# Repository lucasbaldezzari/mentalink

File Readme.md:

# Repositorio Mentalink para competencia BCI

El siguiente repositorio será utilizado para almacenar bibliografía, set de datos, firmware, hardware, imágenes, entre otras cosas, las cuales utilizarán para dictar diferentes talleres y ayduar a los equipos a adquirir y procesar señales de EEG para detectar SSVEPs

## Talleres

- [x] Taller 1: Introducción a las Interfaces Cerebro Computadora
- [x] Taller 2: Introducción a la adquisición y procesamiento de SSVEP
- [x] Taller 3: Introducción a Arduino y Robótica
- [x] Taller 4: Aplicando una CNN para clasificar datos
- [x] Taller 5: Comunicación entre PC y Arduino mediante Python para sincronizar estímulos y recepción/envío de información.  Comunicación entre Python y sitio en HTML para sincronizar estímulos. Protocolo de adquisición de señales de EEG para entrenar clasificadores que serán utilizados en la BCI de manera online. Manejo de versiones en archivos de firmware y hardware.
- [x] Taller 6: Adquisición, procesamiento y almacenamiento de señales de EEG provenientes de la placa Cyton Board de OpenBCI usando Python. Análisis de datos obtenidos luego de la sesión de entrenamiento.

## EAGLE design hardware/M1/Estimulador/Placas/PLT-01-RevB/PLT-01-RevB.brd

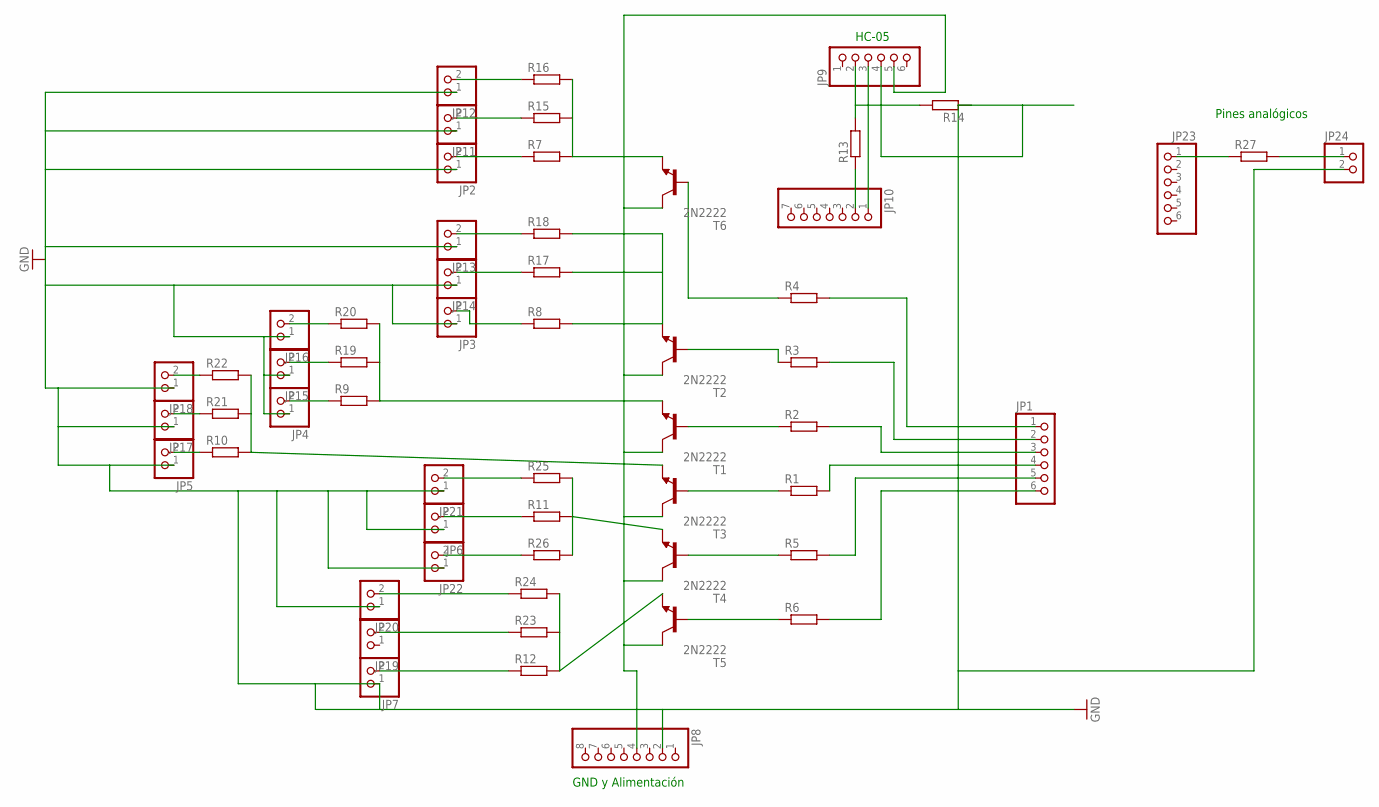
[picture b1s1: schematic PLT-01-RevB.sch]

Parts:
JP1, JP9, JP23: PINHD-1X6; 1X06
JP2, JP3, JP4, JP5, JP6, JP7, JP11, JP12, JP13, JP14, JP15, JP16, JP17, JP18, JP19, JP20, JP21, JP22, JP24: PINHD-1X2; 1X02
JP8: PINHD-1X8; 1X08
JP10: PINHD-1X7; 1X07
R1, R2, R3, R4, R5, R6, R7, R8, R9, R10, R11, R12, R13, R14, R15, R16, R17, R18, R19, R20, R21, R22, R23, R24, R25, R26, R27: R-EU_0207/10; 0207/10
T1, T2, T3, T4, T5, T6: 2N2222; TO92-EBC-OVAL

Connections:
5V: JP8.4, JP9.5, T1.C, T2.C, T3.C, T4.C, T5.C, T6.C
GND: JP2.1, JP3.1, JP4.1, JP5.1, JP6.1, JP7.1, JP8.2, JP9.4, JP11.1, JP12.1, JP13.1, JP14.1, JP15.1, JP16.1, JP17.1, JP18.1, JP20.1, JP21.1, JP22.1, JP24.2, R14.1
unnamed: JP1.1, R4.2
unnamed: JP1.2, R3.2
unnamed: JP1.3, R2.2
unnamed: JP1.4, R1.2
unnamed: JP1.5, R5.2
unnamed: JP1.6, R6.2
unnamed: R6.1, T5.B
unnamed: R5.1, T4.B
unnamed: R1.1, T3.B
unnamed: R2.1, T1.B
unnamed: R3.1, T2.B
unnamed: R4.1, T6.B
unnamed: R7.2, R15.2, R16.2, T6.E
unnamed: JP2.2, R7.1
unnamed: R8.2, R17.2, R18.2, T2.E
unnamed: JP3.2, R8.1
unnamed: R9.2, R19.2, R20.2, T1.E
unnamed: JP4.2, R9.1
unnamed: R10.2, R21.2, R22.2, T3.E
unnamed: JP5.2, R10.1
unnamed: R11.2, R25.2, R26.2, T4.E
unnamed: JP6.2, R11.1
unnamed: R12.2, R23.2, R24.2, T5.E
unnamed: JP7.2, R12.1
unnamed: JP10.2, R13.1
unnamed: JP9.2, R13.2, R14.2
unnamed: JP9.3, JP10.1
unnamed: JP13.2, R18.1
unnamed: JP14.2, R17.1
unnamed: JP17.2, R21.1
unnamed: JP18.2, R22.1
unnamed: JP19.2, R23.1
unnamed: JP20.2, R24.1
unnamed: JP21.2, R25.1
unnamed: JP22.2, R26.1
unnamed: JP12.2, R16.1
unnamed: JP11.2, R15.1
unnamed: JP16.2, R20.1
unnamed: JP15.2, R19.1
unnamed: JP23.1, R27.1
unnamed: JP24.1, R27.2

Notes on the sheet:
Pines analógicos
HC-05
GND y Alimentación

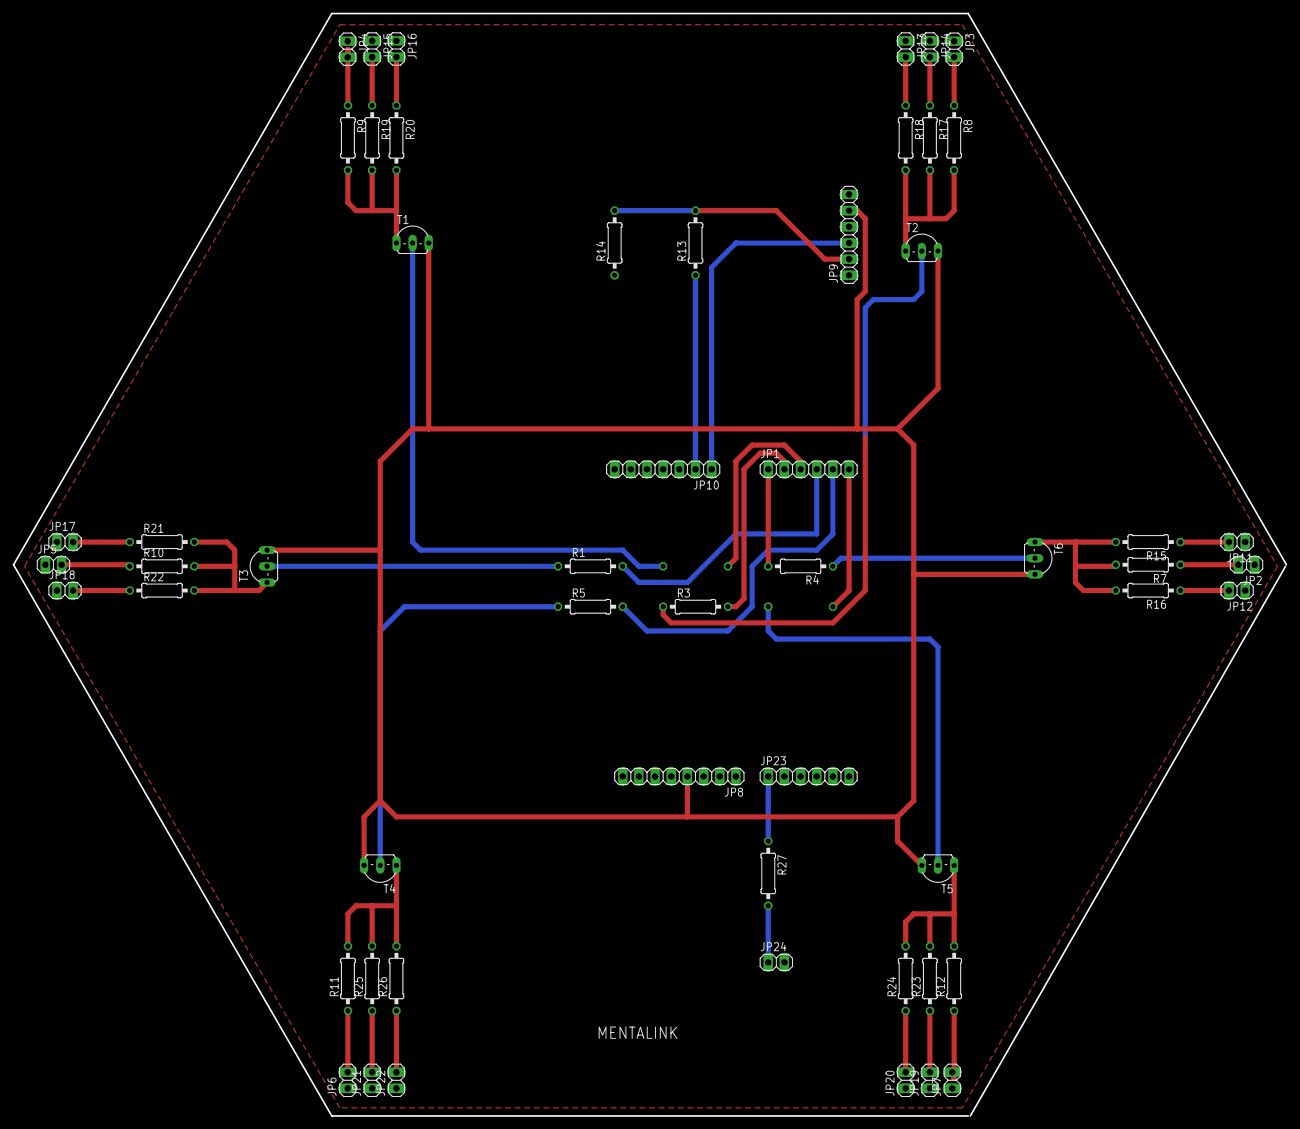
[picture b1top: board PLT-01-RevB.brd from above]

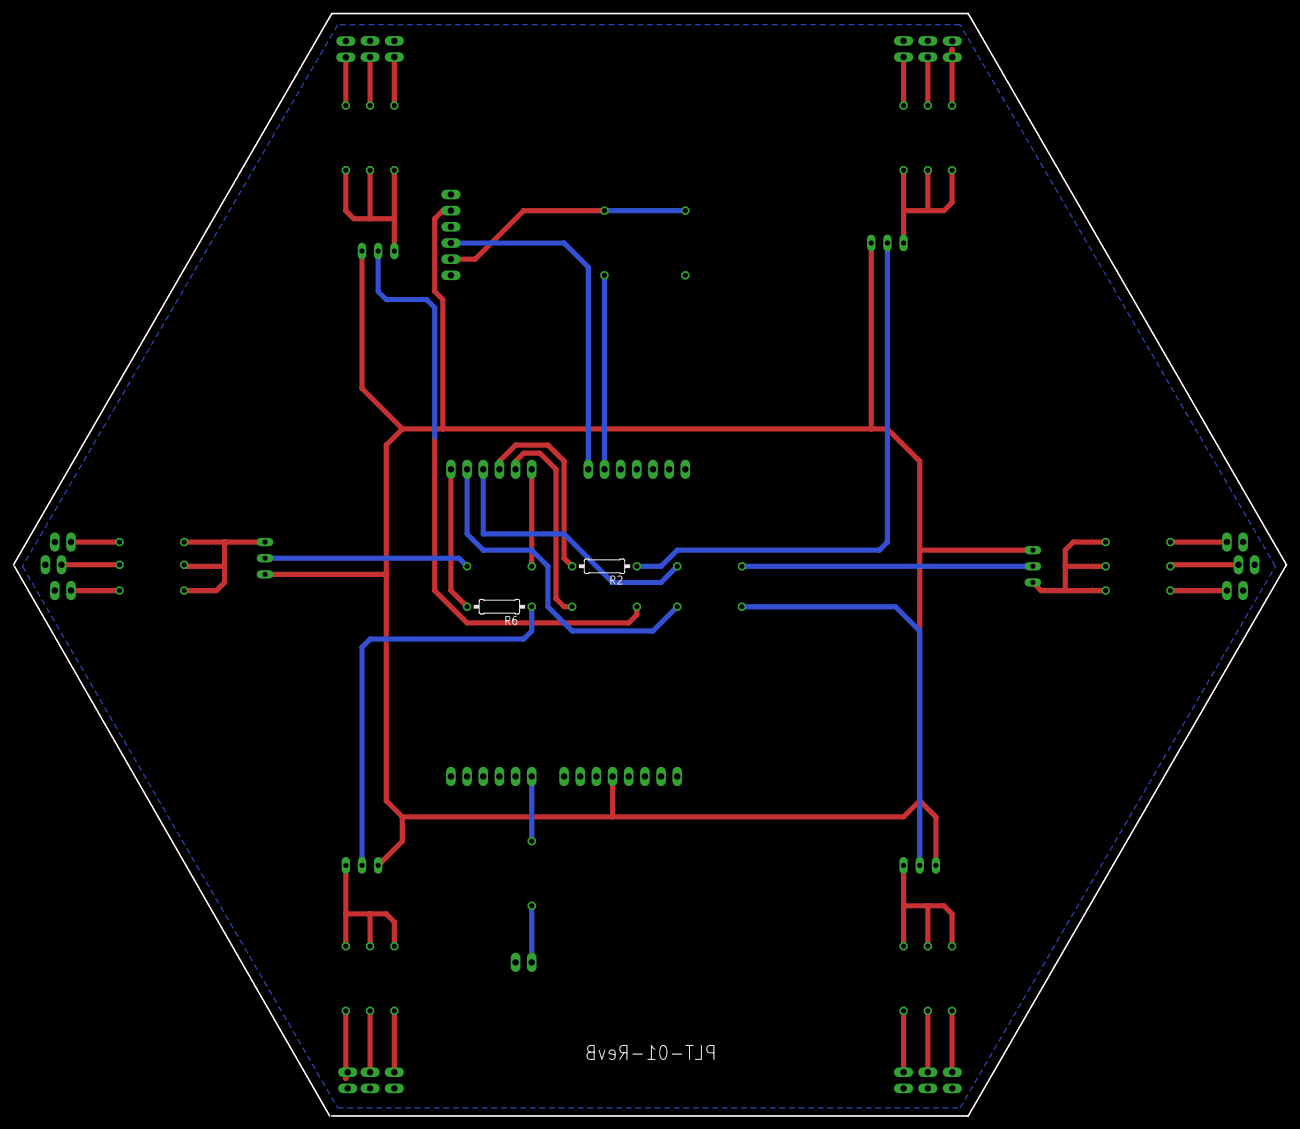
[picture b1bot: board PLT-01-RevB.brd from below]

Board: 2 copper layers, 200.0 x 173.2 mm, 57 parts (2 on the bottom side), 43 nets.

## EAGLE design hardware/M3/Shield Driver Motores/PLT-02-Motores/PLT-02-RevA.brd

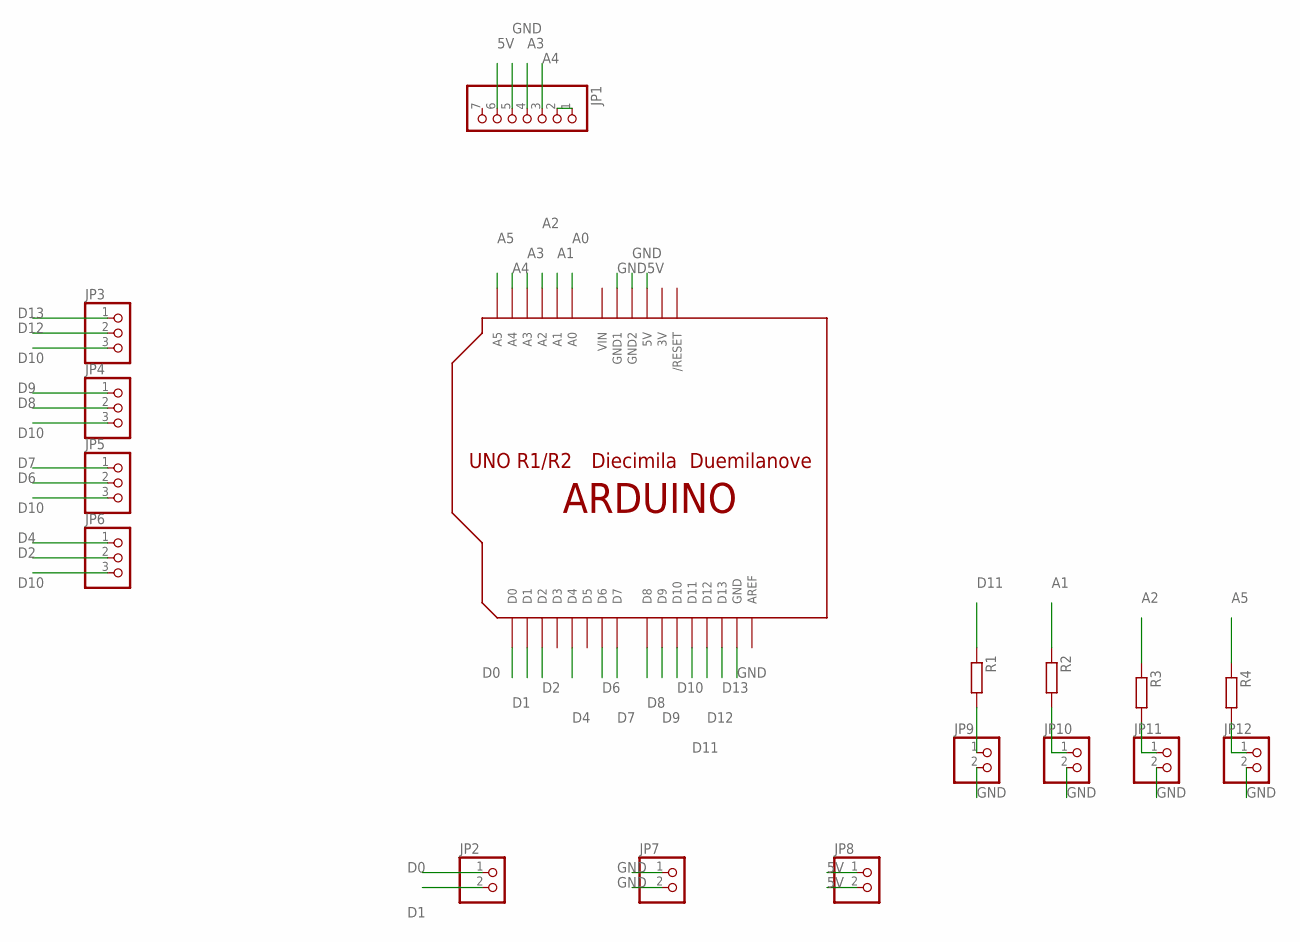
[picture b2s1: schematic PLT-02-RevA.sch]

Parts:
JP1: PINHD-1X7; 1X07
JP2, JP7, JP8, JP9, JP10, JP11, JP12: PINHD-1X2; 1X02
JP3, JP4, JP5, JP6: PINHD-1X3; 1X03
R1, R2, R3, R4: R-EU_0207/10; 0207/10
U$1: ARDUINOUNO; ARDUINO

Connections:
3V: U$1.3V
5V: JP1.6, JP8.1, JP8.2, U$1.5V
A0: U$1.A0
A1: R2.1, U$1.A1
A2: R3.1, U$1.A2
A3: JP1.4, U$1.A3
A4: JP1.3, U$1.A4
A5: R4.1, U$1.A5
D0: JP2.1, U$1.D0
D1: JP2.2, U$1.D1
D2: JP6.2, U$1.D2
D4: JP6.1, U$1.D4
D6: JP5.2, U$1.D6
D7: JP5.1, U$1.D7
D8: JP4.2, U$1.D8
D9: JP4.1, U$1.D9
D10: JP3.3, JP4.3, JP5.3, JP6.3, U$1.D10
D11: R1.1, U$1.D11
D12: JP3.2, U$1.D12
D13: JP3.1, U$1.D13
GND: JP1.5, JP7.1, JP7.2, JP9.2, JP10.2, JP11.2, JP12.2, U$1.GND, U$1.GND1, U$1.GND2
unnamed: JP12.1, R4.2
unnamed: JP10.1, R2.2
unnamed: JP11.1, R3.2
unnamed: JP1.1, JP1.2
unnamed: JP9.1, R1.2
VIN: U$1.VIN

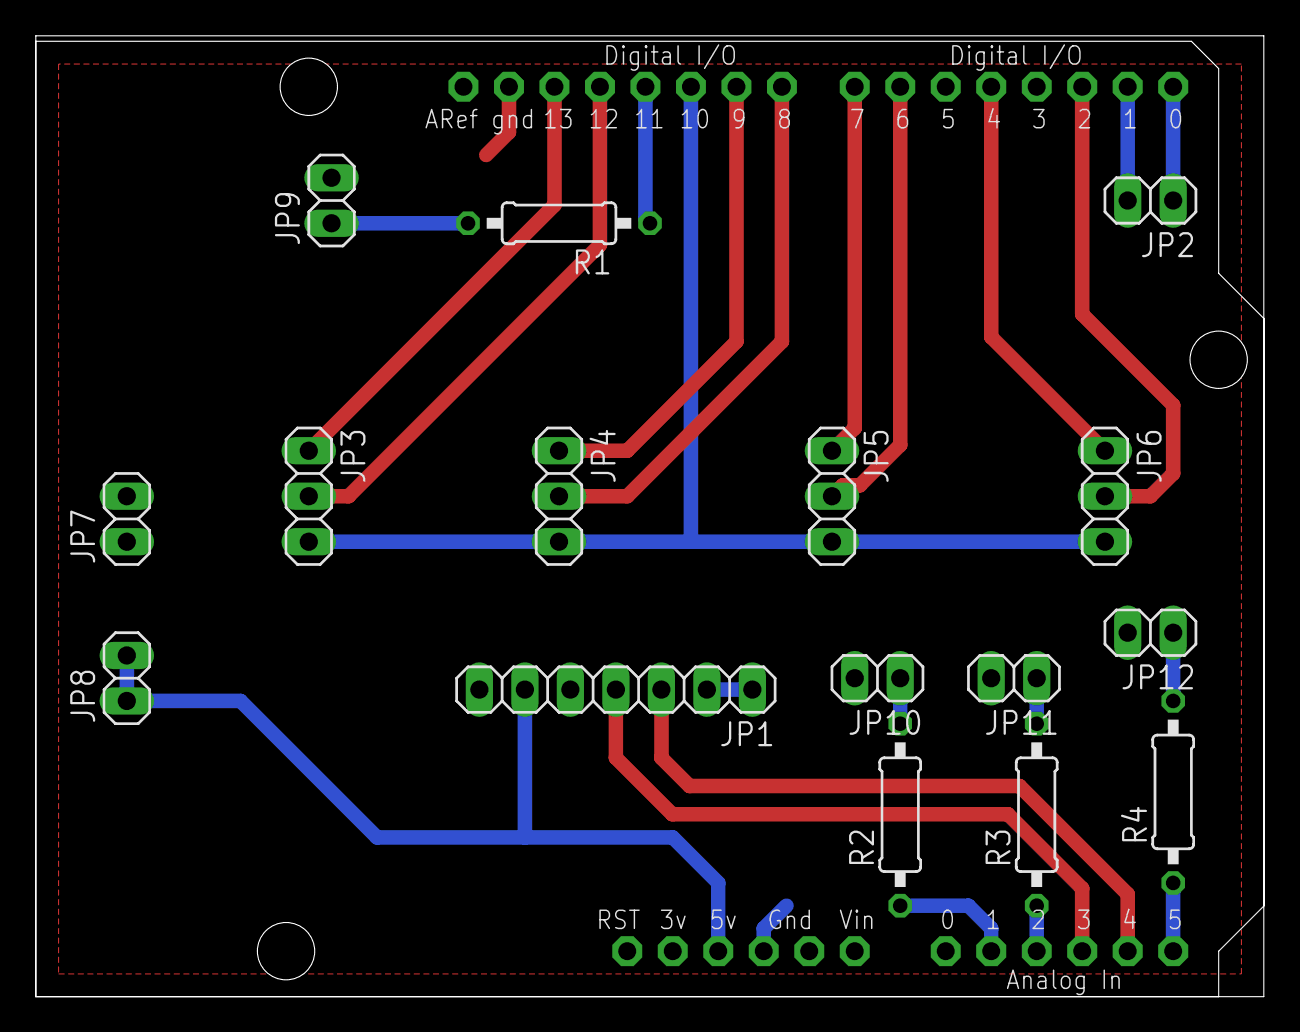
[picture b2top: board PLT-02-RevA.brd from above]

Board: 2 copper layers, 68.6 x 53.6 mm, 17 parts (0 on the bottom side), 24 nets.

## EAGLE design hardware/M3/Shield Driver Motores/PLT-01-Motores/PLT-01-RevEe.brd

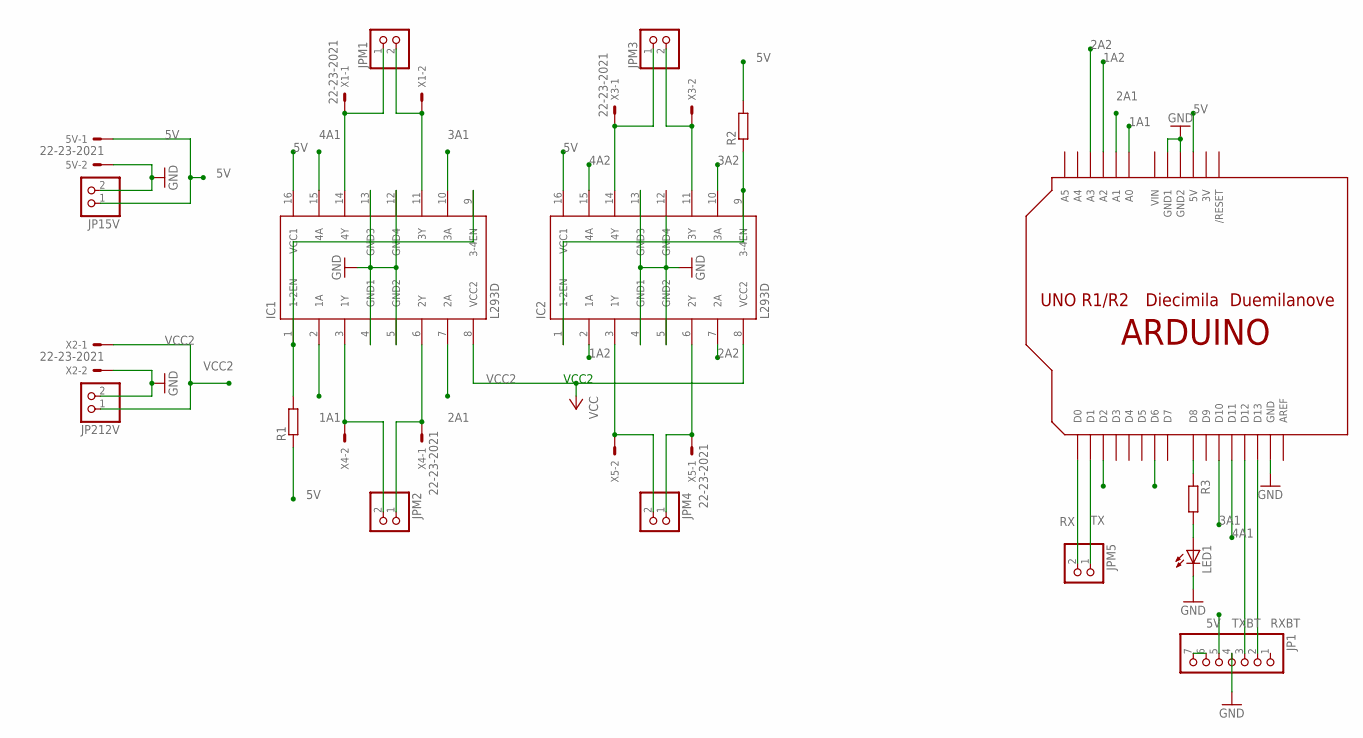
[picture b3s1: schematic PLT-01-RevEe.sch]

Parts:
5V: 22-23-2021
IC1, IC2: L293D; DIL16
JP1: PINHD-1X7; 1X07
JP15V, JP212V: PINHD-1X2; 1X02
JPM1, JPM2, JPM3, JPM4, JPM5: PINHD-1X2; 1X02
LED1: LED5MM
R1, R2, R3: R-EU_0207/10; 0207/10
U$1: ARDUINOUNO; ARDUINO
X1, X2, X3, X4, X5: 22-23-2021

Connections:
1A1: IC1.2 (1A), U$1.A0
1A2: IC2.2 (1A), U$1.A2
2A1: IC1.7 (2A), U$1.A1
2A2: IC2.7 (2A), U$1.A3
3A1: IC1.10 (3A), U$1.D10
3A2: IC2.10 (3A), U$1.D2
3V: U$1.3V
4A1: IC1.15 (4A), U$1.D11
4A2: IC2.15 (4A), U$1.D6
5V: 5V.1, IC1.16 (VCC1), IC2.16 (VCC1), JP1.5, JP15V.1, R1.1, R2.2, U$1.5V
GND: 5V.2, IC1.4 (GND1), IC1.5 (GND2), IC1.12 (GND4), IC1.13 (GND3), IC2.4 (GND1), IC2.5 (GND2), IC2.13 (GND3), JP1.4, JP15V.2, JP212V.2, LED1.K (C), U$1.GND, U$1.GND1, U$1.GND2, X2.2
GND4: IC2.12 (GND4)
unnamed: IC1.3 (1Y), JPM2.2, X4.2
unnamed: IC1.6 (2Y), JPM2.1, X4.1
unnamed: IC2.3 (1Y), JPM4.2, X5.2
unnamed: IC2.6 (2Y), JPM4.1, X5.1
unnamed: IC2.14 (4Y), JPM3.1, X3.1
unnamed: IC2.11 (3Y), JPM3.2, X3.2
unnamed: IC1.14 (4Y), JPM1.1, X1.1
unnamed: IC1.11 (3Y), JPM1.2, X1.2
unnamed: IC2.1 (1-2EN), IC2.9 (3-4EN), R2.1
unnamed: R3.1, U$1.D8
unnamed: IC1.1 (1-2EN), IC1.9 (3-4EN), R1.2
unnamed: LED1.A, R3.2
unnamed: JP1.6, JP1.7
RX: JPM5.2, U$1.D0
RXBT: JP1.2, U$1.D13
TX: JPM5.1, U$1.D1
TXBT: JP1.3, U$1.D12
VCC2: IC1.8 (VCC2), IC2.8 (VCC2), JP212V.1, X2.1
VIN: U$1.VIN

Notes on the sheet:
VCC2

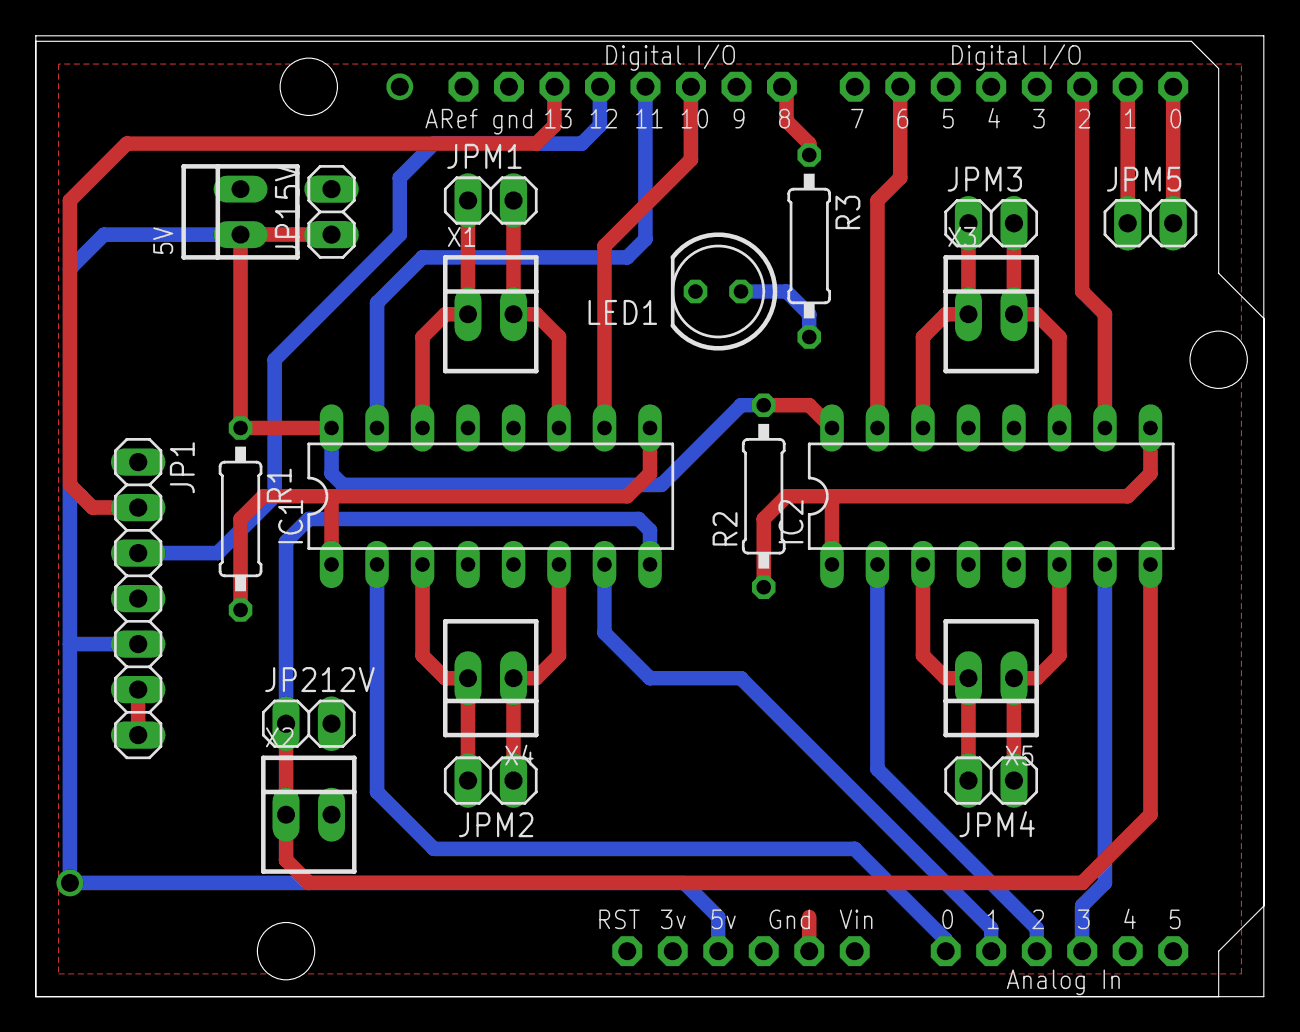
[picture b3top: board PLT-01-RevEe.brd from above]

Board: 2 copper layers, 68.6 x 53.6 mm, 21 parts (0 on the bottom side), 28 nets.

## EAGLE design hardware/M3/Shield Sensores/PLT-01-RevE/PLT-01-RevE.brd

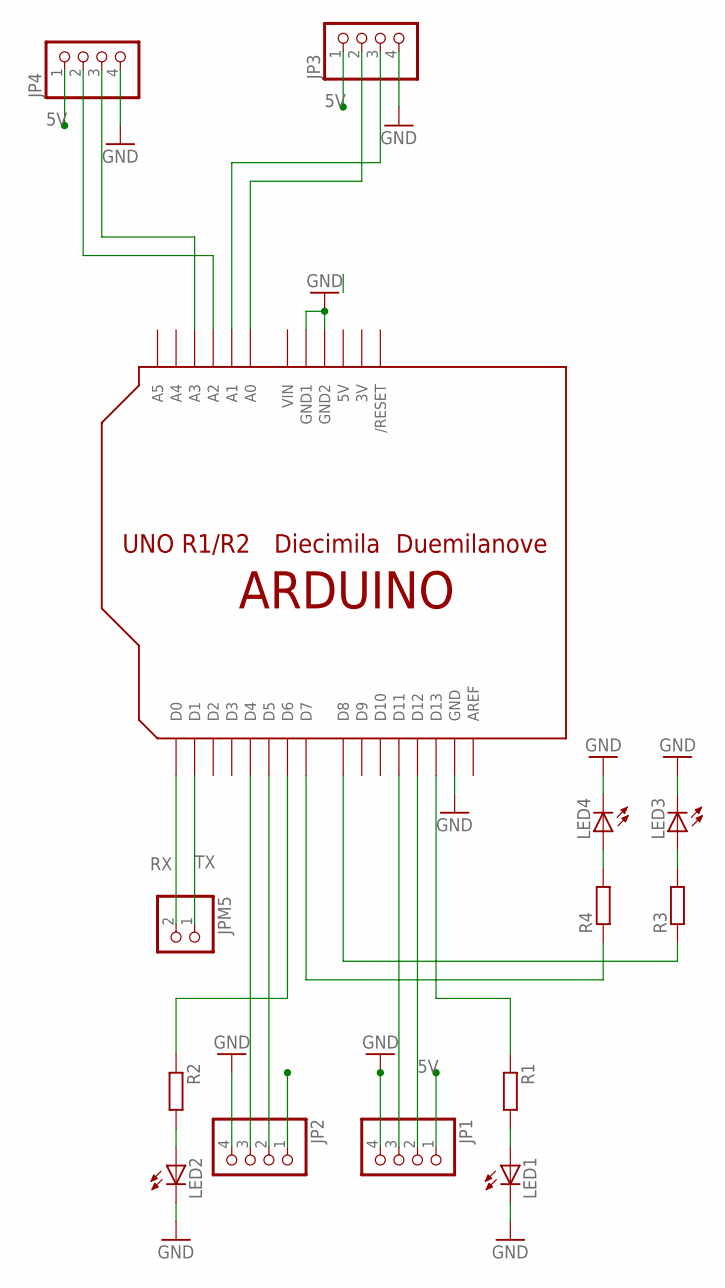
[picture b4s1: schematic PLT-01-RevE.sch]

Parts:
JP1, JP2, JP3, JP4: PINHD-1X4; 1X04
JPM5: PINHD-1X2; 1X02
LED1, LED2, LED3, LED4: LED5MM
R1, R2, R3, R4: R-EU_0207/10; 0207/10
U$1: ARDUINOUNO; ARDUINO

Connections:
3V: U$1.3V
5V: JP1.1, JP2.1, JP3.1, JP4.1, U$1.5V
GND: JP1.4, JP2.4, JP3.4, JP4.4, LED1.K (C), LED2.K (C), LED3.K (C), LED4.K (C), U$1.GND, U$1.GND1, U$1.GND2
unnamed: JP4.3, U$1.A3
unnamed: R4.1, U$1.D7
unnamed: JP2.3, U$1.D4
unnamed: JP2.2, U$1.D5
unnamed: JP4.2, U$1.A2
unnamed: R3.1, U$1.D8
unnamed: JP1.3, U$1.D11
unnamed: JP1.2, U$1.D12
unnamed: R1.1, U$1.D13
unnamed: LED2.A, R2.2
unnamed: LED1.A, R1.2
unnamed: R2.1, U$1.D6
unnamed: LED4.A, R4.2
unnamed: JP3.2, U$1.A0
unnamed: LED3.A, R3.2
unnamed: JP3.3, U$1.A1
RX: JPM5.2, U$1.D0
TX: JPM5.1, U$1.D1
VIN: U$1.VIN

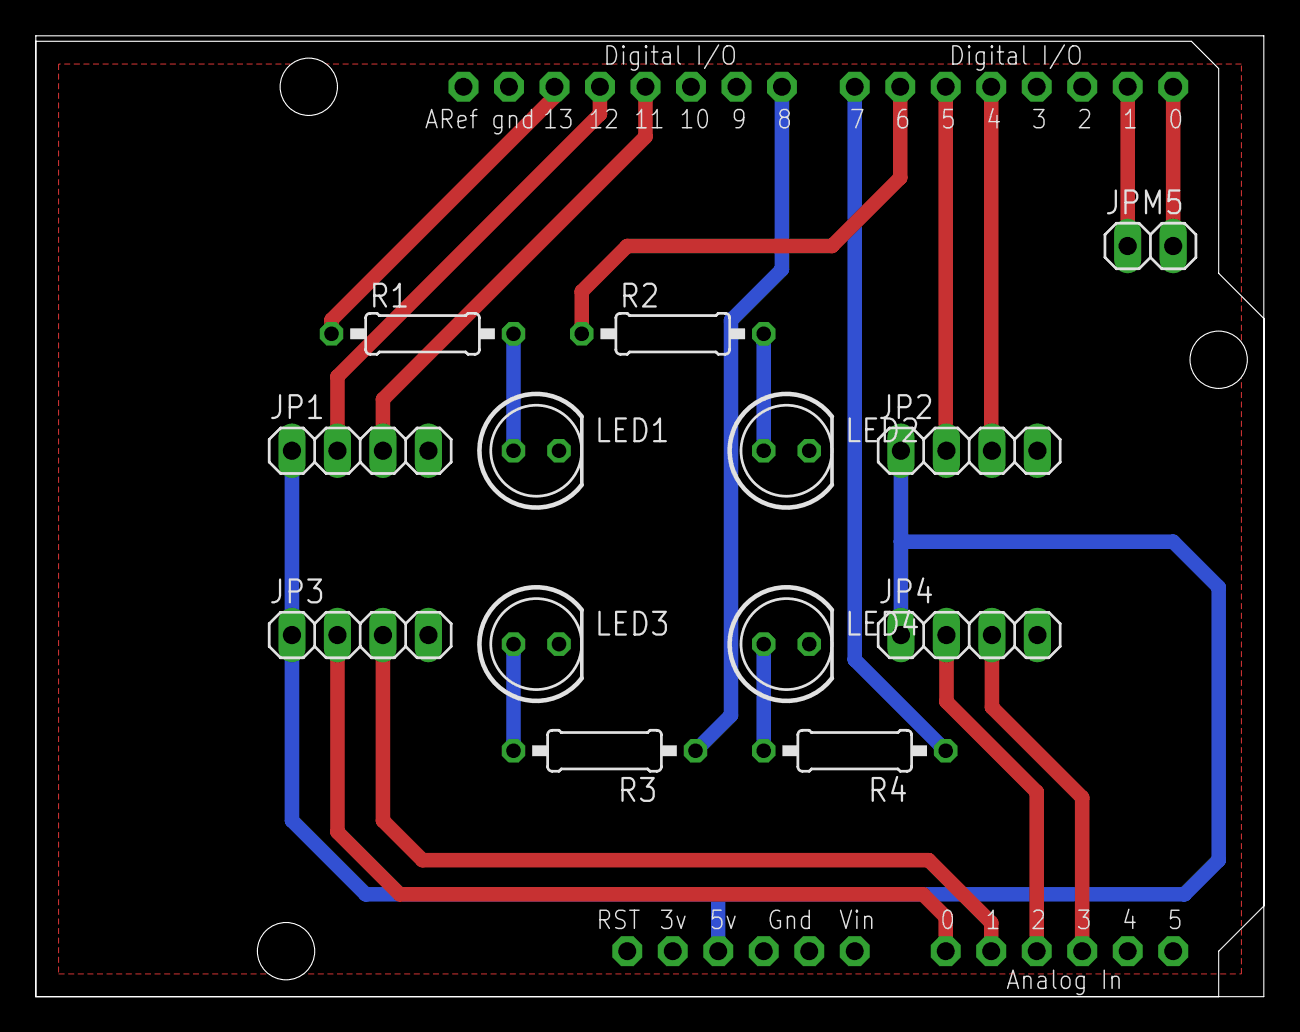
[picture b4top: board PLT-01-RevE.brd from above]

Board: 2 copper layers, 68.6 x 53.6 mm, 14 parts (0 on the bottom side), 20 nets.

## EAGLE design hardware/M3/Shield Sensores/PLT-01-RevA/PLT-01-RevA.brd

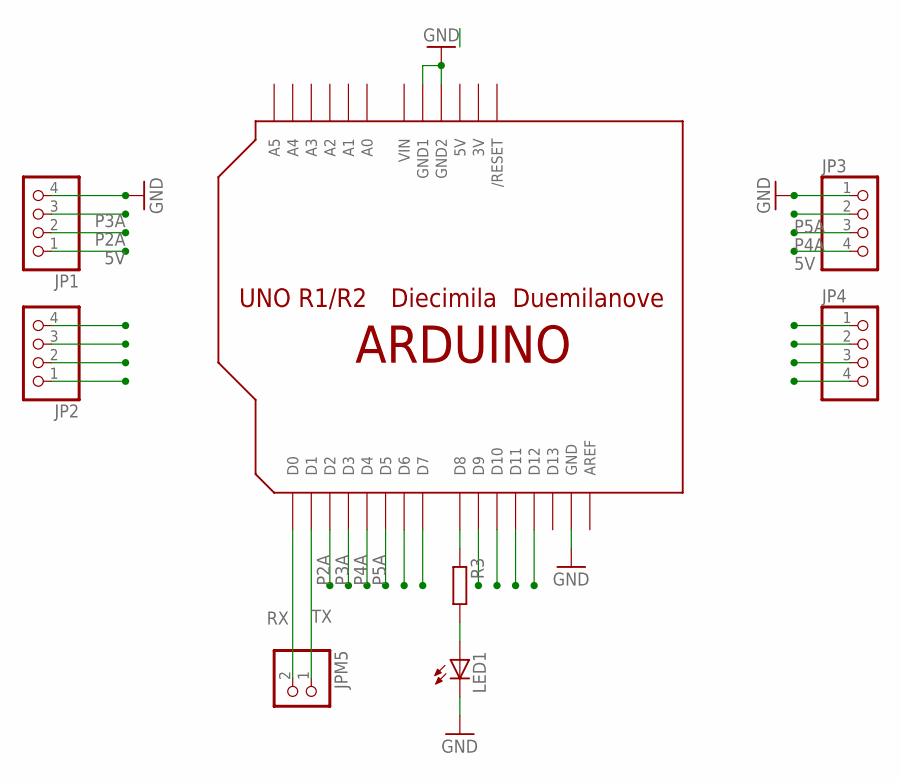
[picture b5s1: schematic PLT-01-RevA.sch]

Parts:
JP1, JP2, JP3, JP4: PINHD-1X4; 1X04
JPM5: PINHD-1X2; 1X02
LED1: LED5MM
R3: R-EU_0207/10; 0207/10
U$1: ARDUINOUNO; ARDUINO

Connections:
3V: U$1.3V
5V: JP1.1, JP3.4, U$1.5V
GND: JP1.4, JP3.1, LED1.K (C), U$1.GND, U$1.GND1, U$1.GND2
unnamed: R3.1, U$1.D8
unnamed: LED1.A, R3.2
P2A: JP1.2, U$1.D2
P3A: JP1.3, U$1.D3
P4A: JP3.3, U$1.D4
P5A: JP3.2, U$1.D5
RX: JPM5.2, U$1.D0
TX: JPM5.1, U$1.D1
VIN: U$1.VIN

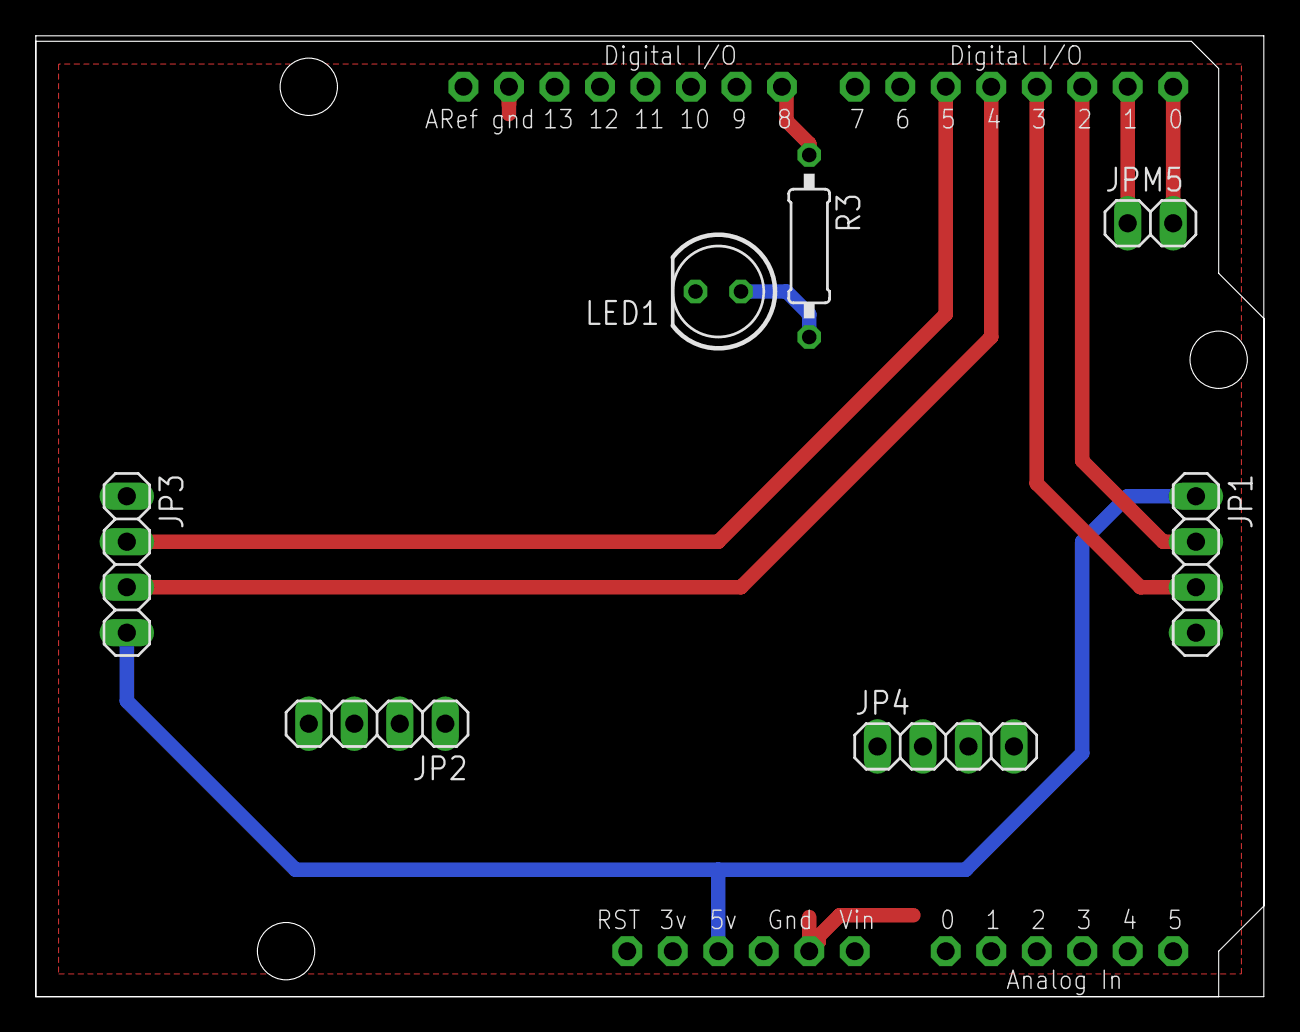
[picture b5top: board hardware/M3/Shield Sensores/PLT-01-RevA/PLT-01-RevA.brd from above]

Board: 2 copper layers, 68.6 x 53.6 mm, 8 parts (0 on the bottom side), 10 nets.

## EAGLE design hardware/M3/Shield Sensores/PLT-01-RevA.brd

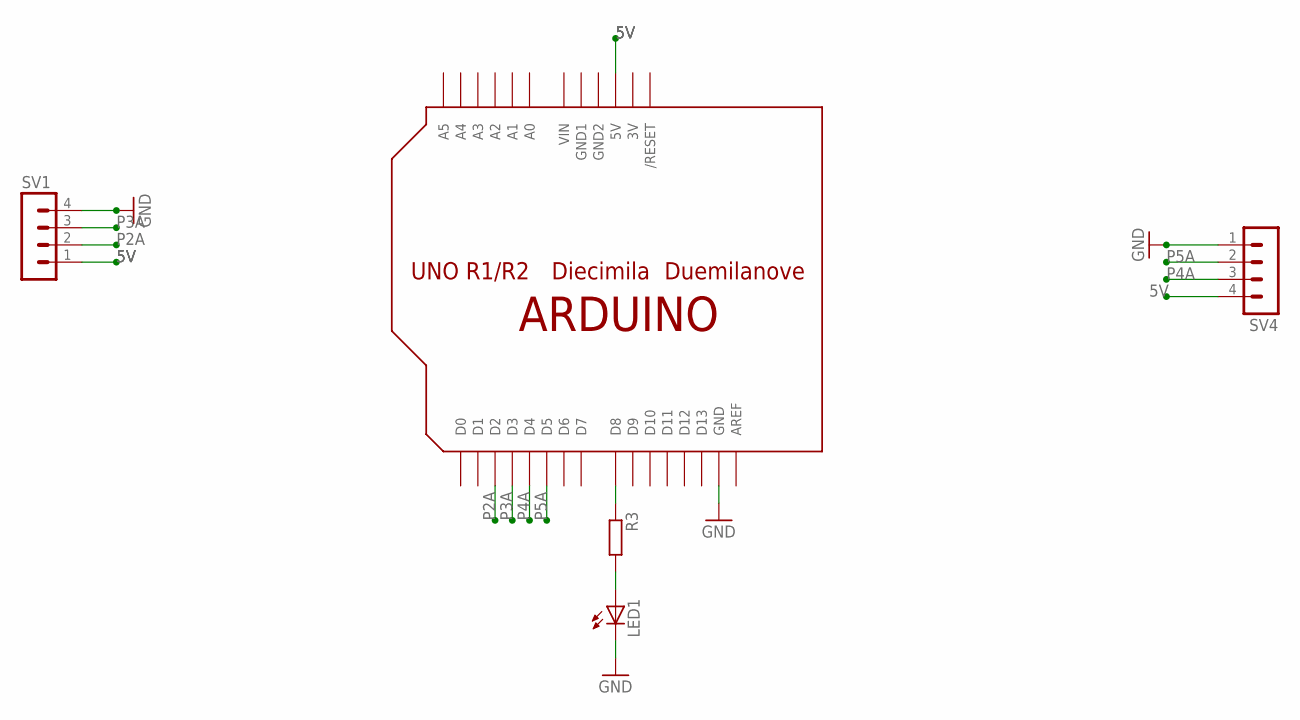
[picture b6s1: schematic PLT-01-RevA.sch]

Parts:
LED1: LED5MM
R3: R-EU_0207/10; 0207/10
SV1, SV4: MA04-1
U$1: ARDUINOUNO; ARDUINO

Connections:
3V: U$1.3V
5V: SV1.1, SV4.4, U$1.5V
GND: LED1.K (C), SV1.4, SV4.1, U$1.GND
GND1: U$1.GND1
GND2: U$1.GND2
unnamed: R3.1, U$1.D8
unnamed: LED1.A, R3.2
P2A: SV1.2, U$1.D2
P3A: SV1.3, U$1.D3
P4A: SV4.3, U$1.D4
P5A: SV4.2, U$1.D5
P6A: U$1.D6
P7A: U$1.D7
VIN: U$1.VIN

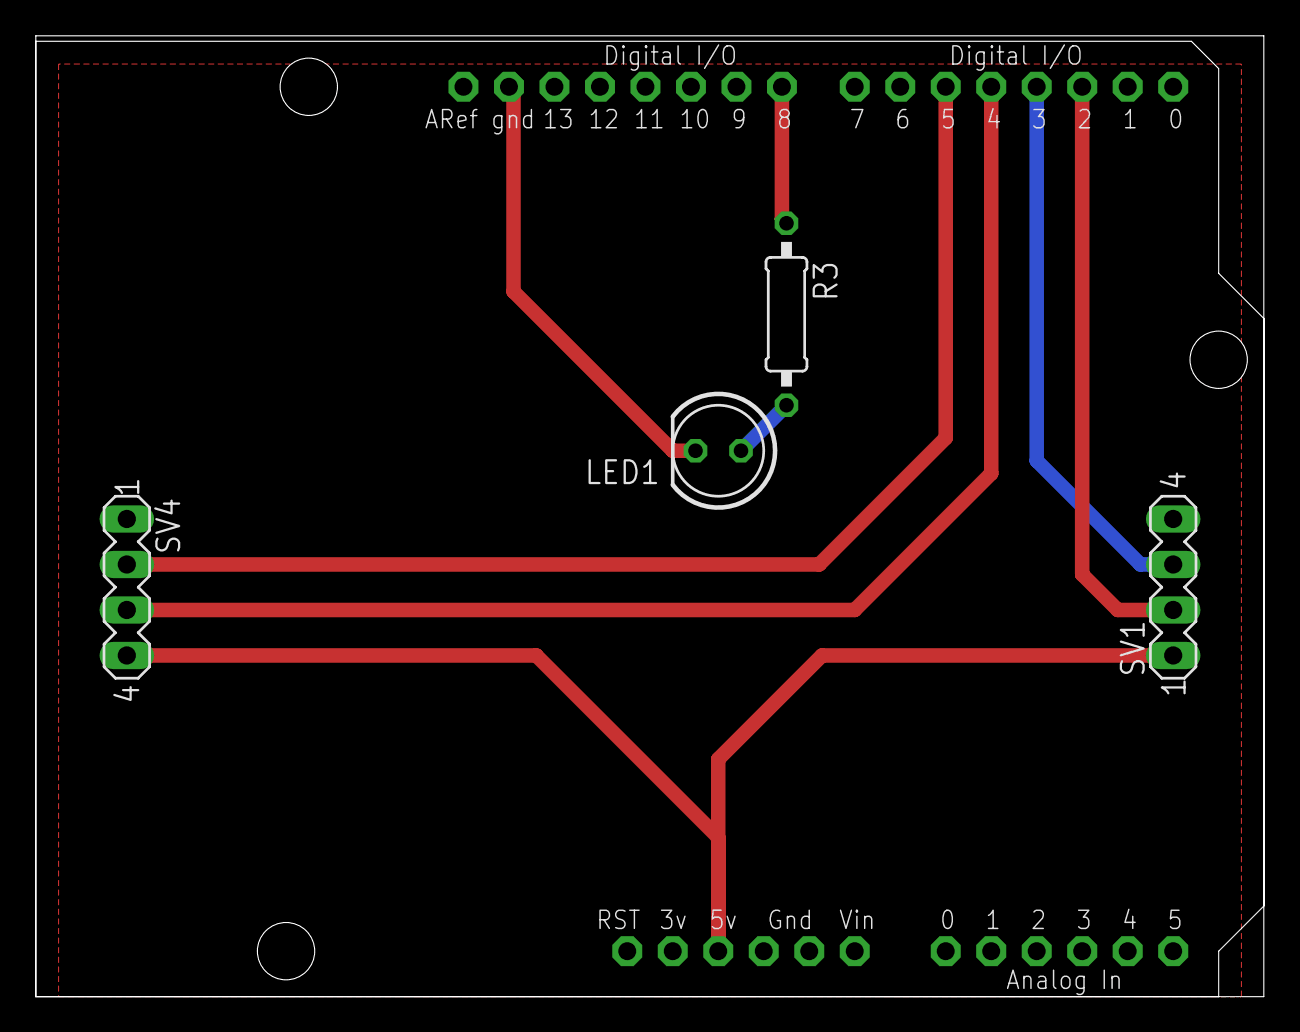
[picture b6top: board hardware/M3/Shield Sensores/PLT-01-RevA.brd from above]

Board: 2 copper layers, 68.6 x 53.6 mm, 5 parts (0 on the bottom side), 8 nets.
